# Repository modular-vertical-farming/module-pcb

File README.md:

# module-pcb
The module pcb files for the modular vertical farming project

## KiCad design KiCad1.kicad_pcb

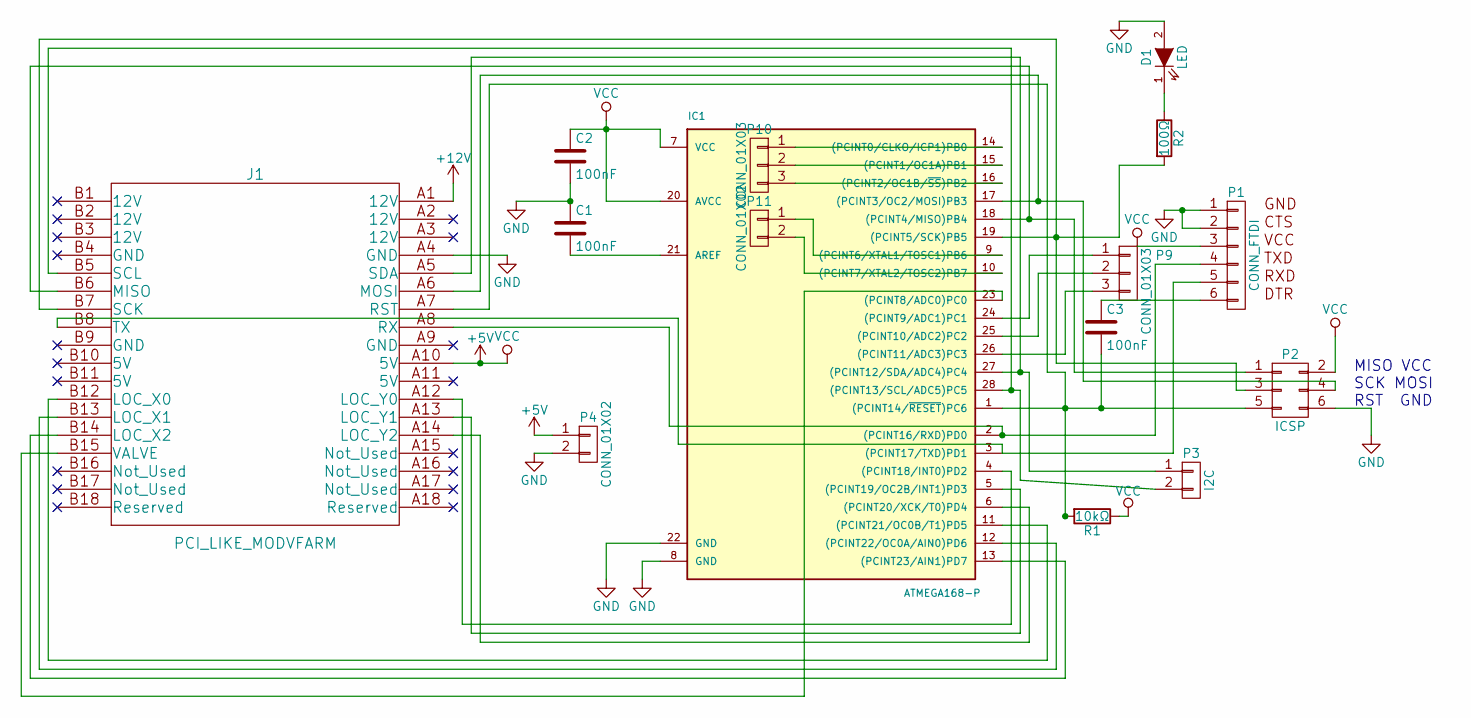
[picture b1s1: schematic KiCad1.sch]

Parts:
C1, C2, C3: 100nF; C_Rect_L7_W2.5_P5
D1: LED; LED-3MM
IC1: ATMEGA168-P; DIP-28__300
J1: PCI_LIKE_MODVFARM; PCI-EXPRESS_NOROUNDED
P1: CONN_FTDI; Pin_Header_Straight_1x06
P2: ICSP; Pin_Header_Straight_2x03
P3: I2C; Pin_Header_Straight_1x02
P4: CONN_01X02; Pin_Header_Straight_1x02
P9, P10: CONN_01X03; Pin_Header_SMD_1x03
P11: CONN_01X02; Pin_Header_SMD_1x02
R1: 10kΩ; Resistor_Horizontal_RM10mm
R2: 100Ω; Resistor_Horizontal_RM10mm

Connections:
+12V: J1.A1 (12V)
GND: C1.1, C2.2, D1.2 (A), IC1.8 (GND), IC1.22 (GND), J1.A4 (GND), P1.1, P1.2, P2.6, P4.2
unnamed: C1.2, IC1.21 (AREF)
unnamed: C3.1, P1.6
unnamed: C3.2, IC1.1 ((PCINT14/~RESET~)PC6), J1.A7 (RST), P2.5, R1.2
unnamed: D1.1 (K), R2.1
unnamed: IC1.2 ((PCINT16/RXD)PD0), J1.A8 (RX), P1.4
unnamed: IC1.3 ((PCINT17/TXD)PD1), J1.B8 (TX), P1.5
unnamed: IC1.4 ((PCINT18/INT0)PD2), J1.A12 (LOC_Y0)
unnamed: IC1.5 ((PCINT19/OC2B/INT1)PD3), J1.A13 (LOC_Y1)
unnamed: IC1.6 ((PCINT20/XCK/T0)PD4), J1.A14 (LOC_Y2)
unnamed: IC1.9 ((PCINT6/XTAL1/TOSC1)PB6), P11.1
unnamed: IC1.10 ((PCINT7/XTAL2/TOSC2)PB7), P11.2
unnamed: IC1.11 ((PCINT21/OC0B/T1)PD5), J1.B12 (LOC_X0)
unnamed: IC1.12 ((PCINT22/OC0A/AIN0)PD6), J1.B13 (LOC_X1)
unnamed: IC1.13 ((PCINT23/AIN1)PD7), J1.B14 (LOC_X2)
unnamed: IC1.14 ((PCINT0/CLKO/ICP1)PB0), P10.1
unnamed: IC1.15 ((PCINT1/OC1A)PB1), P10.2
unnamed: IC1.16 ((PCINT2/OC1B/~SS~)PB2), P10.3
unnamed: IC1.17 ((PCINT3/OC2/MOSI)PB3), J1.A6 (MOSI), P2.4
unnamed: IC1.18 ((PCINT4/MISO)PB4), J1.B6 (MISO), P2.1
unnamed: IC1.19 ((PCINT5/SCK)PB5), J1.B7 (SCK), P2.3, R2.2
unnamed: IC1.23 ((PCINT8/ADC0)PC0), J1.B15 (VALVE)
unnamed: IC1.24 ((PCINT9/ADC1)PC1), P9.1
unnamed: IC1.25 ((PCINT10/ADC2)PC2), P9.2
unnamed: IC1.26 ((PCINT11/ADC3)PC3), P9.3
unnamed: IC1.27 ((PCINT12/SDA/ADC4)PC4), J1.A5 (SDA), P3.1
unnamed: IC1.28 ((PCINT13/SCL/ADC5)PC5), J1.B5 (SCL), P3.2
VCC: C2.1, IC1.7 (VCC), IC1.20 (AVCC), J1.A10 (5V), P1.3, P2.2, P4.1, R1.1

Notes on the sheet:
MISO VCC SCK MOSI RST GND

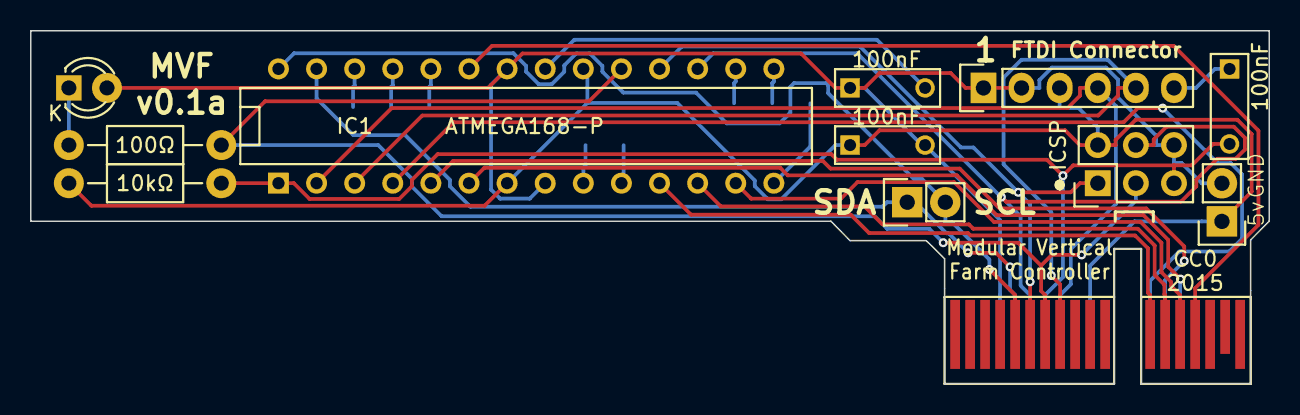
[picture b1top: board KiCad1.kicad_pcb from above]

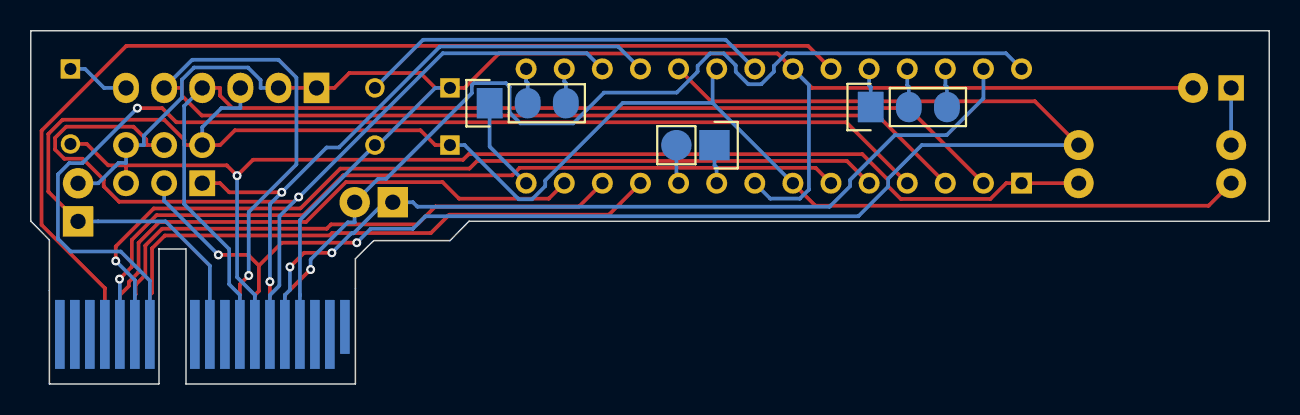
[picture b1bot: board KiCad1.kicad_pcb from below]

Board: 2 copper layers, 82.5 x 23.5 mm, 15 parts (3 on the bottom side), 28 nets.

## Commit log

2015-06-09 Initial Commit (version 0.1a)

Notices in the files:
KiCad1.kicad_pcb:
CC0
